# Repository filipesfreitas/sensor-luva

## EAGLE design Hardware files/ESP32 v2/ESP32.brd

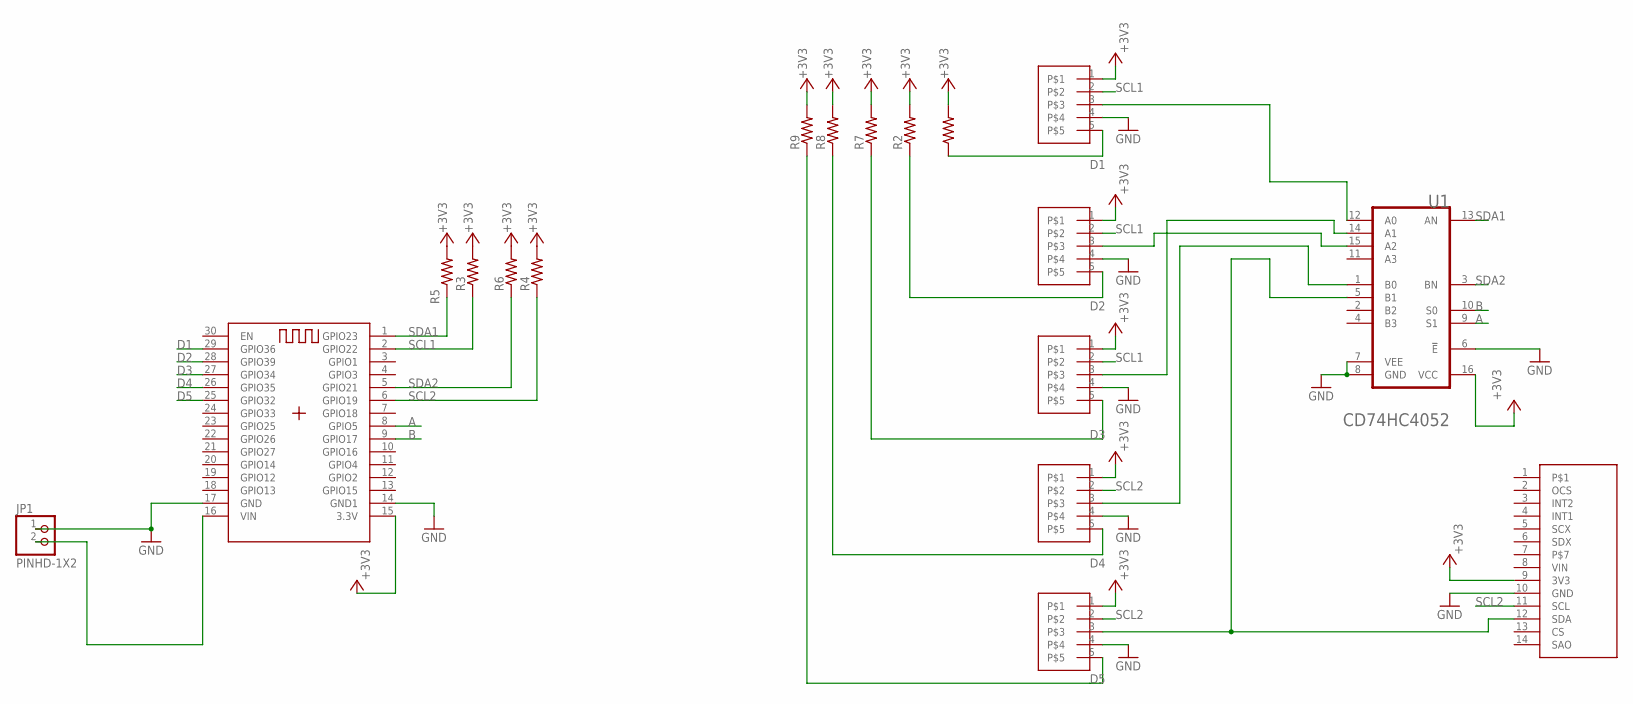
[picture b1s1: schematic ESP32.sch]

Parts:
JP1: PINHD-1X2; 1X02
R1, R2, R5, R6, R7, R8, R9: 10 khom; RES_0805
R3, R4: 10 kohm; RES_0805
U1: TEXAS_INSTRUMENTS_CD74HC4052TEXAS_INSTRUMENTS_CD7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; TEXAS_INSTRUMENTS_CD74HC4052_0
U$1: ESP32ESP32; HDRVR30W70P2540X254_2X15_4572X2794X254B
U$3: BMI160-MODULEBMI160-MODULE; HDRV14W64P1016X254_2X7_1800X1300X838B
U$8, U$9, U$10, U$11, U$12: PHMN4-5PHMN4-51; HDRRA5W70P200_1X5_1200X254X556B

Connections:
+3V3: R1.2, R2.2, R3.2, R4.2, R5.2, R6.2, R7.2, R8.2, R9.2, U1.16 (VCC), U$1.15 (3.3V), U$3.9 (3V3), U$8.1, U$9.1, U$10.1, U$11.1, U$12.1
A: U1.9 (S1), U$1.8 (GPIO5)
B: U1.10 (S0), U$1.9 (GPIO17)
D1: R1.1, U$1.29 (GPIO36), U$8.5
D2: R2.1, U$1.28 (GPIO39), U$9.5
D3: R7.1, U$1.27 (GPIO34), U$10.5
D4: R8.1, U$1.26 (GPIO35), U$11.5
D5: R9.1, U$1.25 (GPIO32), U$12.5
GND: JP1.1, U1.6 (!E!), U1.7 (VEE), U1.8 (GND), U$1.14 (GND1), U$1.17 (GND), U$3.10 (GND), U$8.4, U$9.4, U$10.4, U$11.4, U$12.4
unnamed: JP1.2, U$1.16 (VIN)
unnamed: U1.12 (A0), U$8.3
unnamed: U1.5 (B1), U$3.12 (SDA), U$12.3
unnamed: U1.15 (A2), U$9.3
unnamed: U1.14 (A1), U$10.3
unnamed: U1.1 (B0), U$11.3
SCL1: R3.1, U$1.2 (GPIO22), U$8.2, U$9.2, U$10.2
SCL2: R4.1, U$1.6 (GPIO19), U$3.11 (SCL), U$11.2, U$12.2
SDA1: R5.1, U1.13 (AN), U$1.1 (GPIO23)
SDA2: R6.1, U1.3 (BN), U$1.5 (GPIO21)

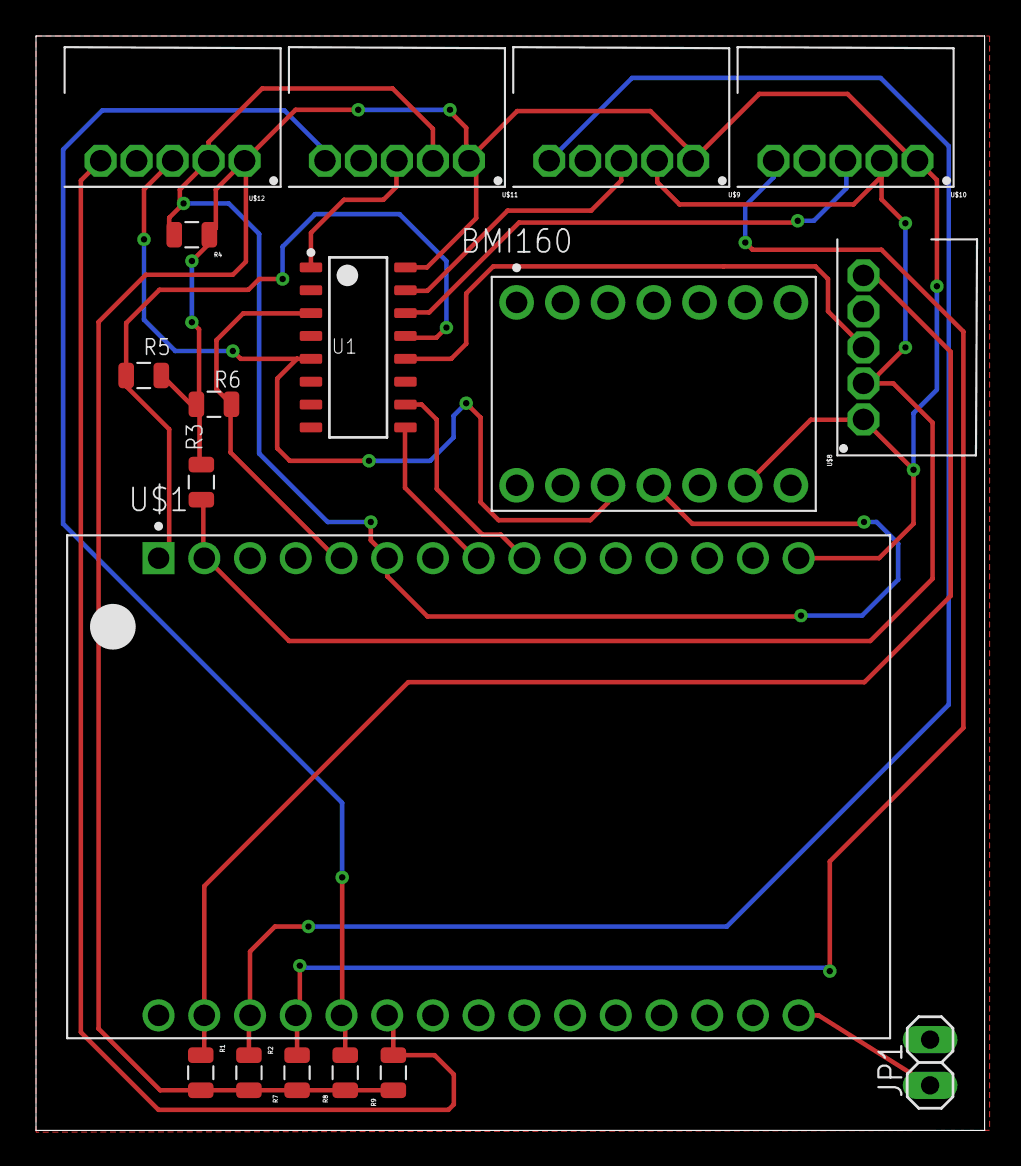
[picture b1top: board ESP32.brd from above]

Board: 2 copper layers, 52.7 x 60.8 mm, 18 parts (0 on the bottom side), 19 nets.

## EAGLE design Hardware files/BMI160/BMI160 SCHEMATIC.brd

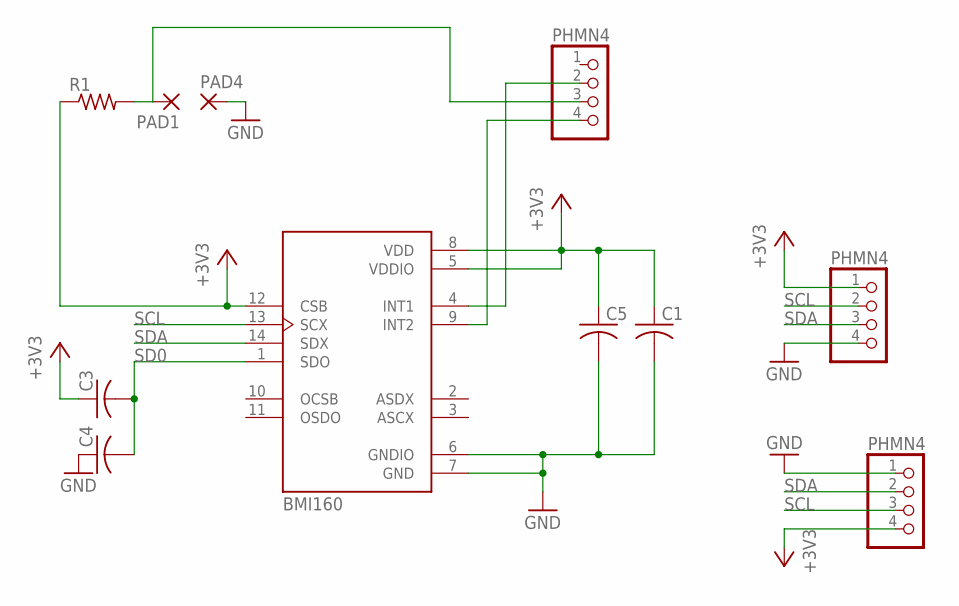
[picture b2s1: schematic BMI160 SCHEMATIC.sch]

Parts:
C1, C3, C4, C5: C-USC0805; C0805
PAD1, PAD4: WIREPADSMD1,27-254; SMD1,27-2,54
R1: CRCW08050000Z0EA; RES_0805
U1: BMI160; PQFN50P300X250X88-14N
U$1, U$2, U$4: PHMN4; 1X04

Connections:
+3V3: C1.1, C3.1, C5.1, R1.1, U1.5 (VDDIO), U1.8 (VDD), U1.12 (CSB), U$1.1, U$2.4
GND: C1.2, C4.1, C5.2, PAD4.1, U1.6 (GNDIO), U1.7 (GND), U$1.4, U$2.1
unnamed: PAD1.1, R1.2, U$4.3
unnamed: U1.9 (INT2), U$4.4
unnamed: U1.4 (INT1), U$4.2
SCL: U1.13 (SCX), U$1.2, U$2.3
SD0: C3.2, C4.2, U1.1 (SDO)
SDA: U1.14 (SDX), U$1.3, U$2.2

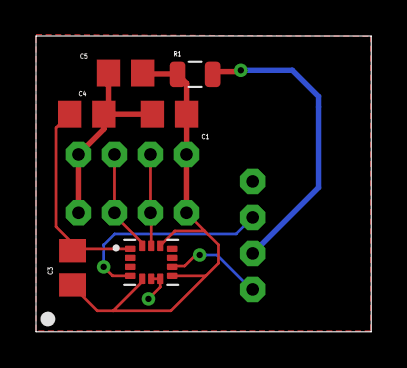
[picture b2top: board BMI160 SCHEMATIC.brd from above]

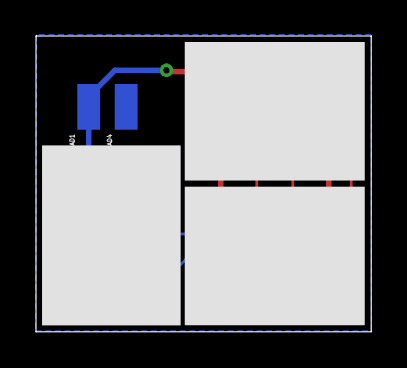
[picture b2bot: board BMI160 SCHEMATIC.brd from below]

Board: 2 copper layers, 18.6 x 16.4 mm, 11 parts (5 on the bottom side), 8 nets.

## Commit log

2020-07-19 Commit inicial script de test em python para leitura e definições importantes do projeto: -acesso pelo bul i2c aos valores de aceleração de um sensor nos 3 eixos próximo passo: - acesso a multiplos s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
2020-07-19 Adicionando documentação do sensos adxl34
    Adicionados datasheet e nota de apliação da fabricante acerca de calibração e uso do sensor ADXL34
2020-07-19 renovando organização diretório
2020-07-19 Seguindo a nota de aplicação AN-1057 foi introduzida no arquivo teste a conversão para graus e os calculos para obtenção das coordenadas esféricas com os ângulos theta e phi.
2020-08-04 RTOS SDK ESP8266
    Filipe de Souza Freitas:
    Add a custom udp servers witch takes data from ADXL345 connected through I2C to an ESP8266-201 and send back to a client
    whom can retrieved it with some nc commands, e.g nc -u 192.168.0.100 3333.
2020-08-25 Change development to esp32
2020-08-25 changed udp project because was related to esp8266
2020-08-25 added i2c task, udp not working properly
2020-08-31 Add event group handle to guarantee synchronism over the data in the packages sent through UDP protocol
2020-09-22 Teste com sensores e movimentacao de um dedo
2020-09-22 scripts de test do matlab
2020-12-01 adicionando código teste do matlab
2021-01-17 ignore build files
2021-01-17 add .git ignore
2021-01-17 removing with filter branch
2021-03-24 Started with Doxygen documentation
2021-03-24 update Doxygen files
2021-03-24 doxygen update
2021-03-28 Add task for resistive sensor reading
2021-03-31 Add test with MPU9250, varing speed of ratation of potentiometer with IMU coupled
2021-04-10 Sensor read test
2021-04-14 Add MPU6050 branch with multiplexer read
2021-04-22 Include adc reding on bus i2c multiplexing on task i2c
2021-05-05 add orientation estimation component
2021-05-07 add task0 for reading A chanel on mux
2021-06-16 fixed complementary filter commit
2021-06-30 Add scripts import files to matlab read data get from the sensor glove device and scripts to plot the data.
2021-06-30 Document and comment the funtions and structures for doxygen documentation type.
2021-07-14 Changed xDelay to defined macro period, that is the period to sample data on all the IMUs and resistance sensors.
2021-09-15 add moving average to adc readings
2021-10-27 fixing: fix adc exponential moving average
2021-10-27 fixing: fix event group control
2021-11-02 testing: change test with sample data and complementary filter parameters
2021-11-05 fixing: clean build files
2021-11-05 git ignore updated to filter doxygen build
2021-11-05 fixing: adc exponential mov average loop
2021-11-05 fixing: changing back, the i aux must start in the length of the samples
2021-11-09 Fixing: Control variable finger for glove structure was updated in a bad way. Changed comparision with channels quantity.
2021-11-13 Fixing: Updated logic to sinchronism of tasks and udp communication. Logic for complementary filter updated too.
2021-11-16 test: imu test data
2021-11-16 test: insert matlab scripts to help visualize test of imu angle
2021-11-16 feature: insert compensation on data in the buffer_arrange function
2022-02-06 Fixing: adc port and channels
2022-02-06 Feature: add new function to handle a single raw daa into orientation
2022-02-06 Clean unused data files and add feature for multiple reading IMUs
2022-02-08 Add FSR calibrated function to compute the force response on the sensor
2022-02-08 dataset moved to fsrdataset folder
2022-02-08 regretion script added
2022-02-09 Tests added
2022-03-10 Feature: add script for curve fitting with fsr dataset
2022-03-10 Configuration: Period of sample changed during tests
2022-03-10 Merge: COmplementary filter solution added.
2022-03-10 Merge: solve untracked files
2022-03-10 Merge: add .gitignore
